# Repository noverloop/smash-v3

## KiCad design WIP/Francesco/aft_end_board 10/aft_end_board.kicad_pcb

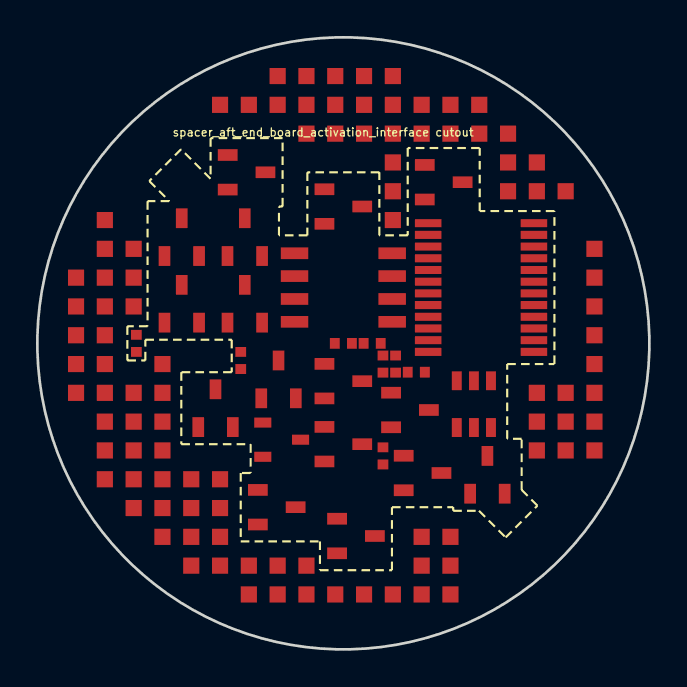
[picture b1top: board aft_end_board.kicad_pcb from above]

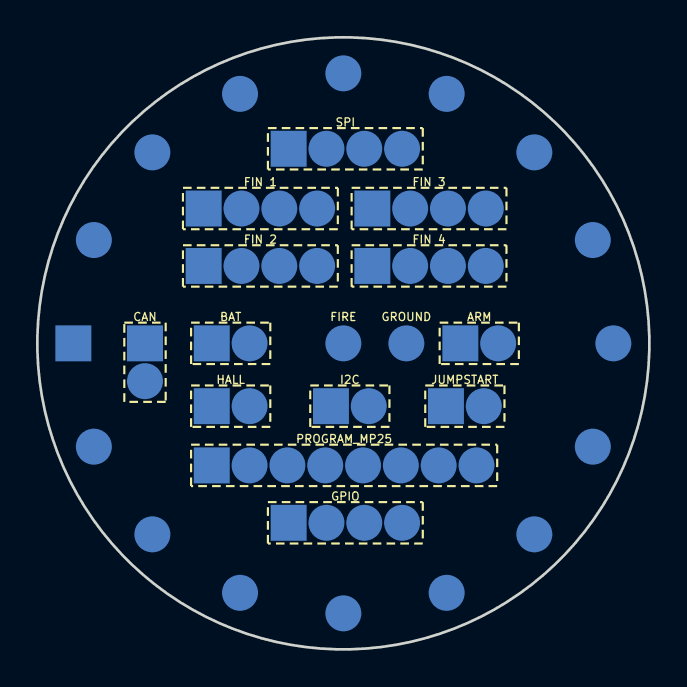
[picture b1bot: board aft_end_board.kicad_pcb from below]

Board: 14 copper layers, 34.0 x 34.0 mm, 91 parts (62 on the bottom side), 82 nets, no tracks yet.

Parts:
C_CAN_GW: C0402 X7R 100nF; Capacitor_SMD_C_0402_1005Metric
J_aft_end_board_spacer_aft_end_board_activation_interface: LGA_lands; J_aft_end_board_spacer_aft_end_board_activation_interface
P_ACT_WIRE_0: P_ACT_WIRE_0; Pogo_Pad_S2.0mm
P_ACT_WIRE_1: P_ACT_WIRE_1; Pogo_Pad_D2.0mm
P_ACT_WIRE_2: P_ACT_WIRE_2; Pogo_Pad_D2.0mm
P_ACT_WIRE_3: P_ACT_WIRE_3; Pogo_Pad_D2.0mm
P_ACT_WIRE_4: P_ACT_WIRE_4; Pogo_Pad_D2.0mm
P_ACT_WIRE_5: P_ACT_WIRE_5; Pogo_Pad_D2.0mm
P_ACT_WIRE_6: P_ACT_WIRE_6; Pogo_Pad_D2.0mm
P_ACT_WIRE_7: P_ACT_WIRE_7; Pogo_Pad_D2.0mm
P_ACT_WIRE_8: P_ACT_WIRE_8; Pogo_Pad_D2.0mm
P_ACT_WIRE_9: P_ACT_WIRE_9; Pogo_Pad_D2.0mm
P_ACT_WIRE_10: P_ACT_WIRE_10; Pogo_Pad_D2.0mm
P_ACT_WIRE_11: P_ACT_WIRE_11; Pogo_Pad_D2.0mm
P_ACT_WIRE_12: P_ACT_WIRE_12; Pogo_Pad_D2.0mm
P_ACT_WIRE_13: P_ACT_WIRE_13; Pogo_Pad_D2.0mm
P_ACT_WIRE_14: P_ACT_WIRE_14; Pogo_Pad_D2.0mm
P_ACT_WIRE_15: P_ACT_WIRE_15; Pogo_Pad_D2.0mm
P_FIRE_COMMON: P_FIRE_COMMON; Pogo_Pad_D2.0mm
Q_FIRE_ARM: DMP6110SVT-7; SOT95P280X100-6N
Q_FIRE_ARM_LS: BSS138LT1G; SOT96P237X111-3N
Q_FIRE_N0, Q_FIRE_N1, Q_FIRE_N2, Q_FIRE_N3, Q_FIRE_N4, Q_FIRE_N5, Q_FIRE_N6, Q_FIRE_N7, Q_FIRE_N8, Q_FIRE_N9, Q_FIRE_N10, Q_FIRE_N11, Q_FIRE_N12, Q_FIRE_N13, Q_FIRE_N14, Q_FIRE_N15: DMN6075SQ-7; SOT96P240X110-3N
R_EXT_CAN_TERM: CRCW0402 120 1% e3; Resistor_SMD_R_0402_1005Metric
R_FIRE_ARM_H: CRCW0402 100k 1% e3; Resistor_SMD_R_0402_1005Metric
R_FIRE_ARM_L: CRCW0402 100k 1% e3; Resistor_SMD_R_0402_1005Metric
R_FIRE_BLEED: CRCW0402 100k 1% e3; Resistor_SMD_R_0402_1005Metric
R_FIRE_MON1: CRCW0402 100k 1% e3; Resistor_SMD_R_0402_1005Metric
R_FIRE_MON2: CRCW0402 11k 1% e3; Resistor_SMD_R_0402_1005Metric
R_JUMP_PAD: CRCW0402 10k 1% e3; Resistor_SMD_R_0402_1005Metric
TP_ACT_CONFIRM: TP_ACT_CONFIRM; Pogo_Pad_S2.0mm
TP_ACT_SET: TP_ACT_SET; Pogo_Pad_D2.0mm
TP_BAT_PROT: TP_BAT_PROT; Pogo_Pad_D2.0mm
TP_BAT_RAW: TP_BAT_RAW; Pogo_Pad_S2.0mm
TP_BOOT0: TP_BOOT0; Pogo_Pad_D2.0mm
TP_CAN_N: TP_CAN_N; Pogo_Pad_S2.0mm
TP_CAN_P: TP_CAN_P; Pogo_Pad_D2.0mm
TP_FIN1_A1: TP_FIN1_A1; Pogo_Pad_S2.0mm
TP_FIN1_A2: TP_FIN1_A2; Pogo_Pad_D2.0mm
TP_FIN1_B1: TP_FIN1_B1; Pogo_Pad_D2.0mm
TP_FIN1_B2: TP_FIN1_B2; Pogo_Pad_D2.0mm
TP_FIN2_A1: TP_FIN2_A1; Pogo_Pad_S2.0mm
TP_FIN2_A2: TP_FIN2_A2; Pogo_Pad_D2.0mm
TP_FIN2_B1: TP_FIN2_B1; Pogo_Pad_D2.0mm
TP_FIN2_B2: TP_FIN2_B2; Pogo_Pad_D2.0mm
TP_FIN3_A1: TP_FIN3_A1; Pogo_Pad_S2.0mm
TP_FIN3_A2: TP_FIN3_A2; Pogo_Pad_D2.0mm
TP_FIN3_B1: TP_FIN3_B1; Pogo_Pad_D2.0mm
TP_FIN3_B2: TP_FIN3_B2; Pogo_Pad_D2.0mm
TP_FIN4_A1: TP_FIN4_A1; Pogo_Pad_S2.0mm
TP_FIN4_A2: TP_FIN4_A2; Pogo_Pad_D2.0mm
TP_FIN4_B1: TP_FIN4_B1; Pogo_Pad_D2.0mm
TP_FIN4_B2: TP_FIN4_B2; Pogo_Pad_D2.0mm
TP_FIN_HALL: TP_FIN_HALL; Pogo_Pad_S2.0mm
TP_GND_ACT: TP_GND_ACT; Pogo_Pad_D2.0mm
TP_GPIO_0: TP_GPIO_0; Pogo_Pad_S2.0mm
TP_GPIO_1: TP_GPIO_1; Pogo_Pad_D2.0mm
TP_GPIO_2: TP_GPIO_2; Pogo_Pad_D2.0mm
TP_GPIO_3: TP_GPIO_3; Pogo_Pad_D2.0mm
TP_HALL_VIN: TP_HALL_VIN; Pogo_Pad_D2.0mm
TP_I2C_SCL: TP_I2C_SCL; Pogo_Pad_D2.0mm
TP_I2C_SDA: TP_I2C_SDA; Pogo_Pad_S2.0mm
TP_JUMP_GND: TP_JUMP_GND; Pogo_Pad_D2.0mm
TP_JUMP_WAKE: TP_JUMP_WAKE; Pogo_Pad_S2.0mm
TP_MP25_GND1: TP_MP25_GND1; Pogo_Pad_D2.0mm
TP_MP25_GND2: TP_MP25_GND2; Pogo_Pad_D2.0mm
TP_NRST: TP_NRST; Pogo_Pad_D2.0mm
TP_SPI_CS_FIN: TP_SPI_CS_FIN; Pogo_Pad_D2.0mm
TP_SPI_MISO: TP_SPI_MISO; Pogo_Pad_D2.0mm
TP_SPI_MOSI: TP_SPI_MOSI; Pogo_Pad_S2.0mm
TP_SPI_SCLK: TP_SPI_SCLK; Pogo_Pad_D2.0mm
TP_SWCLK: TP_SWCLK; Pogo_Pad_D2.0mm
TP_SWDIO: TP_SWDIO; Pogo_Pad_D2.0mm
TP_SWO: TP_SWO; Pogo_Pad_D2.0mm
TP_VDD: TP_VDD; Pogo_Pad_S2.0mm
U_CAN_GW: TCAN1042GVDQ1; SOIC127P600X175-8N
U_FIRE_DEC: CD74HC4514PW; SOP65P640X120-24N

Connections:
3V3: J_aft_end_board_spacer_aft_end_board_ac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.1, J_aft_end_board_spacer_aft_end_board_ac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.45, J_aft_end_board_spacer_aft_end_board_ac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.51, TP_HALL_VIN.1, U_CAN_GW.5
3V3_AON: J_aft_end_board_spacer_aft_end_board_ac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.2, J_aft_end_board_spacer_aft_end_board_ac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.46, TP_VDD.1
ACTIVATE_CONFIRM: J_aft_end_board_spacer_aft_end_board_ac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.3, R_FIRE_MON1.2, R_FIRE_MON2.1, TP_ACT_CONFIRM.1
ACTIVATE_SET: J_aft_end_board_spacer_aft_end_board_ac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.4, Q_FIRE_ARM_LS.1, TP_ACT_SET.1
ACT_WIRE_0: P_ACT_WIRE_0.1, Q_FIRE_N0.3
ACT_WIRE_1: P_ACT_WIRE_1.1, Q_FIRE_N1.3
ACT_WIRE_2: P_ACT_WIRE_2.1, Q_FIRE_N2.3
ACT_WIRE_3: P_ACT_WIRE_3.1, Q_FIRE_N3.3
ACT_WIRE_4: P_ACT_WIRE_4.1, Q_FIRE_N4.3
ACT_WIRE_5: P_ACT_WIRE_5.1, Q_FIRE_N5.3
ACT_WIRE_6: P_ACT_WIRE_6.1, Q_FIRE_N6.3
ACT_WIRE_7: P_ACT_WIRE_7.1, Q_FIRE_N7.3
ACT_WIRE_8: P_ACT_WIRE_8.1, Q_FIRE_N8.3
ACT_WIRE_9: P_ACT_WIRE_9.1, Q_FIRE_N9.3
ACT_WIRE_10: P_ACT_WIRE_10.1, Q_FIRE_N10.3
ACT_WIRE_11: P_ACT_WIRE_11.1, Q_FIRE_N11.3
ACT_WIRE_12: P_ACT_WIRE_12.1, Q_FIRE_N12.3
ACT_WIRE_13: P_ACT_WIRE_13.1, Q_FIRE_N13.3
ACT_WIRE_14: P_ACT_WIRE_14.1, Q_FIRE_N14.3
ACT_WIRE_15: P_ACT_WIRE_15.1, Q_FIRE_N15.3
BAT_PROT: J_aft_end_board_spacer_aft_end_board_ac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.5, J_aft_end_board_spacer_aft_end_board_ac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.47, TP_BAT_PROT.1, U_FIRE_DEC.1, U_FIRE_DEC.24
BAT_RAW: J_aft_end_board_spacer_aft_end_board_ac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.6, J_aft_end_board_spacer_aft_end_board_ac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.48, TP_BAT_RAW.1
BOOT0: J_aft_end_board_spacer_aft_end_board_ac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.7, TP_BOOT0.1
COMP_5V: C_CAN_GW.1, J_aft_end_board_spacer_aft_end_board_ac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.8, J_aft_end_board_spacer_aft_end_board_ac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.49, U_CAN_GW.3
COMP_SWDCLK: J_aft_end_board_spacer_aft_end_board_ac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.9, TP_SWCLK.1
COMP_SWDIO: J_aft_end_board_spacer_aft_end_board_ac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.10, TP_SWDIO.1
EXT_CAN_N: R_EXT_CAN_TERM.2, TP_CAN_N.1, U_CAN_GW.6
EXT_CAN_P: R_EXT_CAN_TERM.1, TP_CAN_P.1, U_CAN_GW.7
EXT_CAN_RX: J_aft_end_board_spacer_aft_end_board_ac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.16, U_CAN_GW.4
EXT_CAN_TX: J_aft_end_board_spacer_aft_end_board_ac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.12, U_CAN_GW.1
FIN1_AOUT1: J_aft_end_board_spacer_aft_end_board_ac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.13, TP_FIN1_A1.1
FIN1_AOUT2: J_aft_end_board_spacer_aft_end_board_ac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.14, TP_FIN1_A2.1
FIN1_BOUT1: J_aft_end_board_spacer_aft_end_board_ac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.15, TP_FIN1_B1.1
FIN1_BOUT2: J_aft_end_board_spacer_aft_end_board_ac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.11, TP_FIN1_B2.1
FIN2_AOUT1: J_aft_end_board_spacer_aft_end_board_ac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.17, TP_FIN2_A1.1
FIN2_AOUT2: J_aft_end_board_spacer_aft_end_board_ac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.18, TP_FIN2_A2.1
FIN2_BOUT1: J_aft_end_board_spacer_aft_end_board_ac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.19, TP_FIN2_B1.1
FIN2_BOUT2: J_aft_end_board_spacer_aft_end_board_ac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.20, TP_FIN2_B2.1
FIN3_AOUT1: J_aft_end_board_spacer_aft_end_board_ac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.21, TP_FIN3_A1.1
FIN3_AOUT2: J_aft_end_board_spacer_aft_end_board_ac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.22, TP_FIN3_A2.1
FIN3_BOUT1: J_aft_end_board_spacer_aft_end_board_ac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.23, TP_FIN3_B1.1
FIN3_BOUT2: J_aft_end_board_spacer_aft_end_board_ac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.24, TP_FIN3_B2.1
FIN4_AOUT1: J_aft_end_board_spacer_aft_end_board_ac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.25, TP_FIN4_A1.1
FIN4_AOUT2: J_aft_end_board_spacer_aft_end_board_ac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.30, TP_FIN4_A2.1
FIN4_BOUT1: J_aft_end_board_spacer_aft_end_board_ac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.27, TP_FIN4_B1.1
FIN4_BOUT2: J_aft_end_board_spacer_aft_end_board_ac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.26, TP_FIN4_B2.1
FIN_HALL: J_aft_end_board_spacer_aft_end_board_ac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.29, TP_FIN_HALL.1
FIRE_ARMED: P_FIRE_COMMON.1, Q_FIRE_ARM.1, Q_FIRE_ARM.2, Q_FIRE_ARM.5, Q_FIRE_ARM.6
FIRE_ARM_G: Q_FIRE_ARM.3, R_FIRE_ARM_H.2, R_FIRE_ARM_L.1
FIRE_ARM_GD: Q_FIRE_ARM_LS.3, R_FIRE_ARM_L.2
FIRE_HV: J_aft_end_board_spacer_aft_end_board_ac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.28, J_aft_end_board_spacer_aft_end_board_ac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.50, Q_FIRE_ARM.4, R_FIRE_ARM_H.1, R_FIRE_BLEED.1, R_FIRE_MON1.1
FLEX_GND: C_CAN_GW.2, J_aft_end_board_spacer_aft_end_board_ac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.31, J_aft_end_board_spacer_aft_end_board_ac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.52, J_aft_end_board_spacer_aft_end_board_ac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.53, J_aft_end_board_spacer_aft_end_board_ac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.54, J_aft_end_board_spacer_aft_end_board_ac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.55, J_aft_end_board_spacer_aft_end_board_ac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.56, J_aft_end_board_spacer_aft_end_board_ac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.57, J_aft_end_board_spacer_aft_end_board_ac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.58, J_aft_end_board_spacer_aft_end_board_ac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.59, J_aft_end_board_spacer_aft_end_board_ac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.60, J_aft_end_board_spacer_aft_end_board_ac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.61, J_aft_end_board_spacer_aft_end_board_ac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.62, J_aft_end_board_spacer_aft_end_board_ac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.63, J_aft_end_board_spacer_aft_end_board_ac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.64, J_aft_end_board_spacer_aft_end_board_ac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.65, J_aft_end_board_spacer_aft_end_board_ac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.66, J_aft_end_board_spacer_aft_end_board_ac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.67, J_aft_end_board_spacer_aft_end_board_ac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.68, J_aft_end_board_spacer_aft_end_board_ac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.69, J_aft_end_board_spacer_aft_end_board_ac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.70, J_aft_end_board_spacer_aft_end_board_ac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.71, J_aft_end_board_spacer_aft_end_board_ac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.72, J_aft_end_board_spacer_aft_end_board_ac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.73, J_aft_end_board_spacer_aft_end_board_ac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.74, J_aft_end_board_spacer_aft_end_board_ac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.75, J_aft_end_board_spacer_aft_end_board_ac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.76, J_aft_end_board_spacer_aft_end_board_ac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.77, J_aft_end_board_spacer_aft_end_board_ac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.78, J_aft_end_board_spacer_aft_end_board_ac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.79, J_aft_end_board_spacer_aft_end_board_ac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.80, J_aft_end_board_spacer_aft_end_board_ac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.81, J_aft_end_board_spacer_aft_end_board_ac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.82, J_aft_end_board_spacer_aft_end_board_ac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.83, J_aft_end_board_spacer_aft_end_board_ac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.84, J_aft_end_board_spacer_aft_end_board_ac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.85, J_aft_end_board_spacer_aft_end_board_ac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.86, J_aft_end_board_spacer_aft_end_board_ac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.87, J_aft_end_board_spacer_aft_end_board_ac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.88, J_aft_end_board_spacer_aft_end_board_ac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.89, J_aft_end_board_spacer_aft_end_board_ac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.90, J_aft_end_board_spacer_aft_end_board_ac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.91, J_aft_end_board_spacer_aft_end_board_ac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.92, J_aft_end_board_spacer_aft_end_board_ac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.93, J_aft_end_board_spacer_aft_end_board_ac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.94, J_aft_end_board_spacer_aft_end_board_ac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.95, J_aft_end_board_spacer_aft_end_board_ac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.96, J_aft_end_board_spacer_aft_end_board_ac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.97, J_aft_end_board_spacer_aft_end_board_ac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.98, Q_FIRE_ARM_LS.2, Q_FIRE_N0.2, Q_FIRE_N1.2, Q_FIRE_N2.2, Q_FIRE_N3.2, Q_FIRE_N4.2, Q_FIRE_N5.2, Q_FIRE_N6.2, Q_FIRE_N7.2, Q_FIRE_N8.2, Q_FIRE_N9.2, Q_FIRE_N10.2, Q_FIRE_N11.2, Q_FIRE_N12.2, Q_FIRE_N13.2, Q_FIRE_N14.2, Q_FIRE_N15.2, R_FIRE_BLEED.2, R_FIRE_MON2.2, TP_GND_ACT.1, TP_JUMP_GND.1, TP_MP25_GND1.1, TP_MP25_GND2.1, U_CAN_GW.2, U_CAN_GW.8, U_FIRE_DEC.12, U_FIRE_DEC.23
GPIO_EXT_0: J_aft_end_board_spacer_aft_end_board_ac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.32, TP_GPIO_0.1, U_FIRE_DEC.2
GPIO_EXT_1: J_aft_end_board_spacer_aft_end_board_ac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.33, TP_GPIO_1.1, U_FIRE_DEC.3
GPIO_EXT_2: J_aft_end_board_spacer_aft_end_board_ac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.34, TP_GPIO_2.1, U_FIRE_DEC.21
GPIO_EXT_3: J_aft_end_board_spacer_aft_end_board_ac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.35, TP_GPIO_3.1, U_FIRE_DEC.22
JUMP_PAD: R_JUMP_PAD.1, TP_JUMP_WAKE.1
JUMP_WAKE: J_aft_end_board_spacer_aft_end_board_ac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.36, R_JUMP_PAD.2
NRST: J_aft_end_board_spacer_aft_end_board_ac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.37, TP_NRST.1
SWO: J_aft_end_board_spacer_aft_end_board_ac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.38, TP_SWO.1
SYS_I2C_SCL: J_aft_end_board_spacer_aft_end_board_ac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.39, TP_I2C_SCL.1
SYS_I2C_SDA: J_aft_end_board_spacer_aft_end_board_ac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.40, TP_I2C_SDA.1
SYS_SPI_CS_FIN: J_aft_end_board_spacer_aft_end_board_ac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.41, TP_SPI_CS_FIN.1
SYS_SPI_MISO: J_aft_end_board_spacer_aft_end_board_ac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.42, TP_SPI_MISO.1
SYS_SPI_MOSI: J_aft_end_board_spacer_aft_end_board_ac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.43, TP_SPI_MOSI.1
SYS_SPI_SCLK: J_aft_end_board_spacer_aft_end_board_ac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.44, TP_SPI_SCLK.1
Y0_FIRE_SEL: Q_FIRE_N0.1, U_FIRE_DEC.11
Y1_FIRE_SEL: Q_FIRE_N1.1, U_FIRE_DEC.9
Y2_FIRE_SEL: Q_FIRE_N2.1, U_FIRE_DEC.10
Y3_FIRE_SEL: Q_FIRE_N3.1, U_FIRE_DEC.8
Y4_FIRE_SEL: Q_FIRE_N4.1, U_FIRE_DEC.7
Y5_FIRE_SEL: Q_FIRE_N5.1, U_FIRE_DEC.6
Y6_FIRE_SEL: Q_FIRE_N6.1, U_FIRE_DEC.5
Y7_FIRE_SEL: Q_FIRE_N7.1, U_FIRE_DEC.4
Y8_FIRE_SEL: Q_FIRE_N8.1, U_FIRE_DEC.18
Y9_FIRE_SEL: Q_FIRE_N9.1, U_FIRE_DEC.17
Y10_FIRE_SEL: Q_FIRE_N10.1, U_FIRE_DEC.20
Y11_FIRE_SEL: Q_FIRE_N11.1, U_FIRE_DEC.19
Y12_FIRE_SEL: Q_FIRE_N12.1, U_FIRE_DEC.14
Y13_FIRE_SEL: Q_FIRE_N13.1, U_FIRE_DEC.13
Y14_FIRE_SEL: Q_FIRE_N14.1, U_FIRE_DEC.16
Y15_FIRE_SEL: Q_FIRE_N15.1, U_FIRE_DEC.15
